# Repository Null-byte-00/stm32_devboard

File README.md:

# Custom Designed STM32F401CCU6 Dev Board
This is a 4 layer STM32F401CCU6 Dev Board I designed and sent for fabrication and assembly at JLCPCB<br>
the picture of the board's front and back:<br>
<br>
It still has a few problems I mentioned later in this document.
## Schematic and pcb layout
the board was designed with kicad. It has 4 layers including a ground plane, power plane and 2 signal layer.<br>
circuit schematic:<br>
<br>
a view of pcb layout:<br>
<br>
Kicad 3d viewer:<br>

## Problems with this version
Since the design was rushed and this being my first microcontroller design there are a few problems with this version I'm trying to solve in later iterations.<br><br>
1. Wrong oscillator and USB connection
I chose the wrong oscillator for the board's high speed clock. and since stm32's usb connection requires a clock multiple of 1MHz to establish a USB connection, this board is unable to interact through USB.<br>
And since I didn't add a SWD connector, the only way to program the board is with a UART to USB connector connected to the board's UART pins.<br>
But the board still needs to be powered by USB.<br>
Here's a picture of the board connected to my laptop through a UARD-to-USB module:<br>
<br><br>
2. there are a few mistakes on the silkscreen<br><br>
3. the position files are auto generated and I had to adjust them before sending for assembly
## Video
See this youtube video for more information about this project:<br>
https://www.youtube.com/shorts/pBtifo1SFRY

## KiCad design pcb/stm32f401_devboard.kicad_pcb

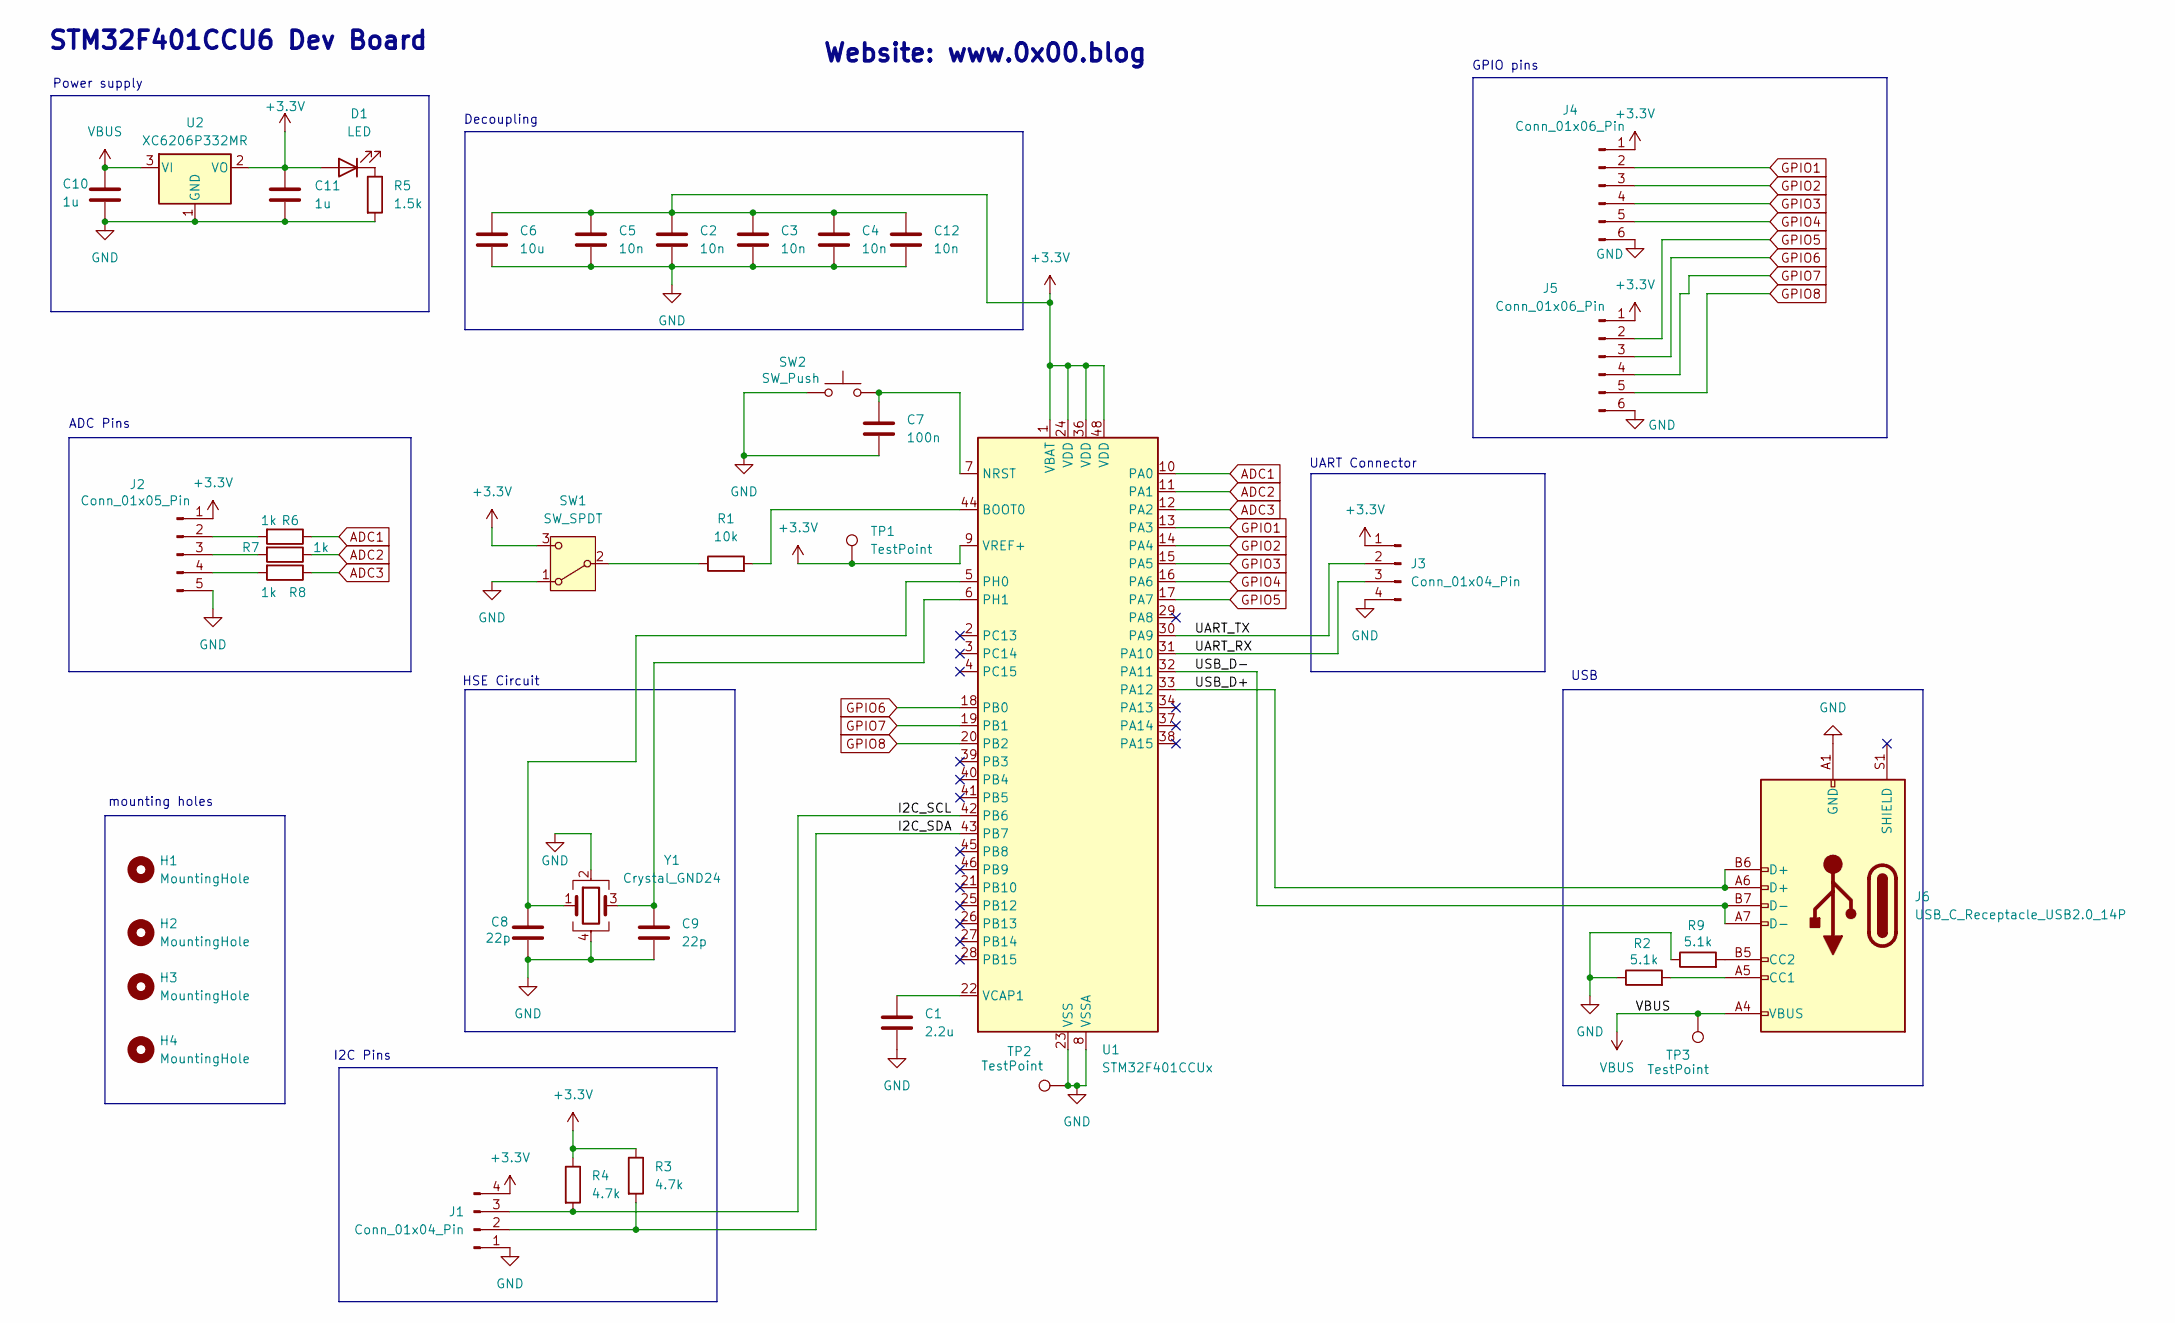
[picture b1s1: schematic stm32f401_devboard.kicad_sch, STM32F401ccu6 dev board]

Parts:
C1: 2.2u; C_1206_3216Metric
C2, C3, C4, C5, C12: 10n; C_0402_1005Metric
C6: 10u; C_1206_3216Metric
C7: 100n; C_0603_1608Metric
C8, C9: 22p; C_0402_1005Metric
C10, C11: 1u; C_0603_1608Metric
D1: LED; LED_0603_1608Metric
H1, H2, H3, H4: MountingHole; MountingHole_2.1mm
J1, J3: Conn_01x04_Pin; PinHeader_1x04_P2.54mm_Vertical
J2: Conn_01x05_Pin; PinHeader_1x05_P2.54mm_Vertical
J4, J5: Conn_01x06_Pin; PinHeader_1x06_P2.54mm_Vertical
J6: USB_C_Receptacle_USB2.0_14P; USB_C_Receptacle_HRO_TYPE-C-31-M-12
R1: 10k; R_1206_3216Metric
R2, R9: 5.1k; R_0603_1608Metric
R3, R4: 4.7k; R_0805_2012Metric
R5: 1.5k; R_0805_2012Metric
R6, R7, R8: 1k; R_0402_1005Metric
SW1: SW_SPDT; SW-TH_K3-1293S-E2
SW2: SW_Push; SW_TS-1088_XNP
TP1, TP2, TP3: TestPoint; TestPoint_Pad_D1.5mm
U1: STM32F401CCUx; QFN-48-1EP_7x7mm_P0.5mm_EP5.6x5.6mm
U2: XC6206P332MR; SOT-23-3
Y1: Crystal_GND24; Crystal_SMD_3225-4Pin_3.2x2.5mm

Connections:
+3.3V: C2.1, C3.1, C4.1, C5.1, C6.1, C11.1, C12.1, D1.2 (A), J1.4, J2.1, J3.1, J4.1, J5.1, R3.1, R4.1, SW1.3 (C), TP1.1, U1.1 (VBAT), U1.9 (VREF+), U1.24 (VDD), U1.36 (VDD), U1.48 (VDD), U2.2 (VO)
/I2C_SCL: J1.3, R4.2, U1.42 (PB6)
/I2C_SDA: J1.2, R3.2, U1.43 (PB7)
/UART_RX: J3.3, U1.31 (PA10)
/UART_TX: J3.2, U1.30 (PA9)
/USB_D+: J6.A6 (D+), J6.B6 (D+), U1.33 (PA12)
/USB_D-: J6.A7 (D-), J6.B7 (D-), U1.32 (PA11)
ADC1: R6.1, U1.10 (PA0)
ADC2: R7.1, U1.11 (PA1)
ADC3: R8.1, U1.12 (PA2)
GND: C1.2, C2.2, C3.2, C4.2, C5.2, C6.2, C7.2, C8.2, C9.2, C10.2, C11.2, C12.2, J1.1, J2.5, J3.4, J4.6, J5.6, J6.A1 (GND), J6.A12 (GND), J6.B1 (GND), J6.B12 (GND), R2.1, R5.2, R9.1, SW1.1 (A), SW2.1, TP2.1, U1.8 (VSSA), U1.23 (VSS), U1.35 (VSS), U1.47 (VSS), U1.49 (VSS), U2.1 (GND), Y1.2, Y1.4
GPIO1: J4.2, U1.13 (PA3)
GPIO2: J4.3, U1.14 (PA4)
GPIO3: J4.4, U1.15 (PA5)
GPIO4: J4.5, U1.16 (PA6)
GPIO5: J5.2, U1.17 (PA7)
GPIO6: J5.3, U1.18 (PB0)
GPIO7: J5.4, U1.19 (PB1)
GPIO8: J5.5, U1.20 (PB2)
unnamed: D1.1 (K), R5.1
unnamed: J2.2, R6.2
unnamed: J2.3, R7.2
unnamed: J2.4, R8.2
unnamed: J6.A5 (CC1), R2.2
unnamed: J6.B5 (CC2), R9.2
unnamed: R1.1, SW1.2 (B)
unnamed: R1.2, U1.44 (BOOT0)
unnamed: C7.1, SW2.2, U1.7 (NRST)
unnamed: C8.1, U1.5 (PH0), Y1.1
unnamed: C9.1, U1.6 (PH1), Y1.3
unnamed: C1.1, U1.22 (VCAP1)
VBUS: C10.1, J6.A4 (VBUS), J6.A9 (VBUS), J6.B4 (VBUS), J6.B9 (VBUS), TP3.1, U2.3 (VI)

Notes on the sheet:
Decoupling
USB
HSE Circuit
STM32F401CCU6 Dev Board
UART Connector
I2C Pins
mounting holes
Power supply
Website: www.0x00.blog
GPIO pins
ADC Pins

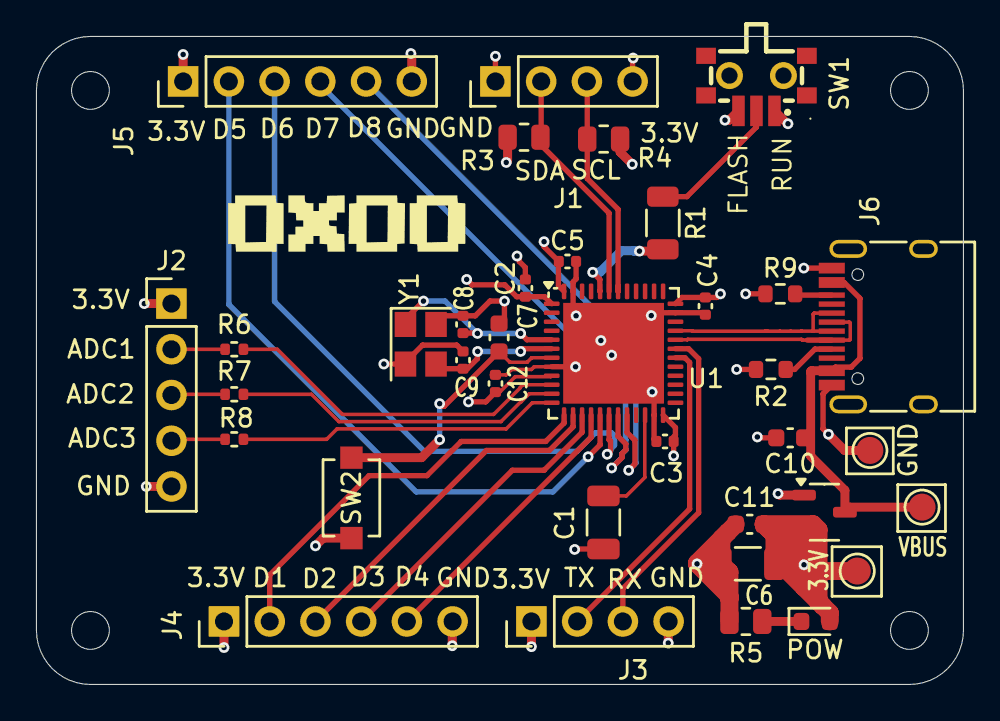
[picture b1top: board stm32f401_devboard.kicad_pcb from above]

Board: 4 copper layers, 51.5 x 36.0 mm, 40 parts (0 on the bottom side), 32 nets.

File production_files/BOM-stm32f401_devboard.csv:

Comment,Designator,Footprint,LCSC,Quantity
TestPoint,TP3,TestPoint_Pad_D1.5mm,,1
TestPoint,TP2,TestPoint_Pad_D1.5mm,,1
2.2u,C1,C_1206_3216Metric,C50254,1
SW_Push,SW2,SW_TS-1088_XNP,C720477,1
5.1k,R9,R_0603_1608Metric,C23186,1
USB_C_Receptacle_USB2.0_14P,J6,USB_C_Receptacle_HRO_TYPE-C-31-M-12,C165948,1
5.1k,R2,R_0603_1608Metric,C23186,1
Conn_01x06_Pin,J5,PinHeader_1x06_P2.54mm_Vertical,,1
Conn_01x06_Pin,J4,PinHeader_1x06_P2.54mm_Vertical,,1
Conn_01x04_Pin,J3,PinHeader_1x04_P2.54mm_Vertical,,1
Conn_01x05_Pin,J2,PinHeader_1x05_P2.54mm_Vertical,,1
Conn_01x04_Pin,J1,PinHeader_1x04_P2.54mm_Vertical,,1
10n,C3,C_0402_1005Metric,C1524,1
SW_SPDT,SW1,K3-1296S-E2_HRO,C145852,1
Crystal_GND24,Y1,Crystal_SMD_3225-4Pin_3.2x2.5mm,C160454,1
XC6206P332MR,U2,SOT-23-3,C5446,1
1k,R8,R_0402_1005Metric,C11702,1
1k,R6,R_0402_1005Metric,C11702,1
1.5k,R5,R_0805_2012Metric,C4310,1
4.7k,R4,R_0805_2012Metric,C17673,1
4.7k,R3,R_0805_2012Metric,C17673,1
10k,R1,R_1206_3216Metric,C17902,1
LED,D1,LED_0603_1608Metric,C2290,1
10n,C12,C_0402_1005Metric,C1524,1
1u,C11,C_0603_1608Metric,C15849,1
1u,C10,C_0603_1608Metric,C15849,1
22p,C9,C_0402_1005Metric,C1555,1
22p,C8,C_0402_1005Metric,C1555,1
100n,C7,C_0603_1608Metric,C14663,1
10u,C6,C_1206_3216Metric,C13585,1
10n,C5,C_0402_1005Metric,C1524,1
10n,C4,C_0402_1005Metric,C1524,1
10n,C2,C_0402_1005Metric,C1524,1
STM32F401CCUx,U1,QFN-48-1EP_7x7mm_P0.5mm_EP5.6x5.6mm,C79861,1
TestPoint,TP1,TestPoint_Pad_D1.5mm,,1
1k,R7,R_0402_1005Metric,C11702,1
